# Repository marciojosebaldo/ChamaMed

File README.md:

# ChamaMed
Protótipo de gestão de solicitações de atendimento da enfermagem por parte de pacientes internados em leitos hospitalares.

Recursos:
- Arduino Mega 2560;
- protoboard 830 pontos;
- módulo RFID RC522;
- condutores;
- 3 LEDs 3mm;
- 3 resistores de 680;
- 6 reguladores de 5V (o envio do sinal era de 12V);
- 1 bipe de placa-mãe desktop;
- 1 cabo USB;

Recurso autoral:
- Placa de circuito impresso com relé, transistor 13007 NPN, fotoacoplador, resistor de 220ohm, resistor de 680ohm, conector jack de força PJ-102 horizontal, micro botão de pressão NA, LED 3mm e 3 conectores fêmeas.

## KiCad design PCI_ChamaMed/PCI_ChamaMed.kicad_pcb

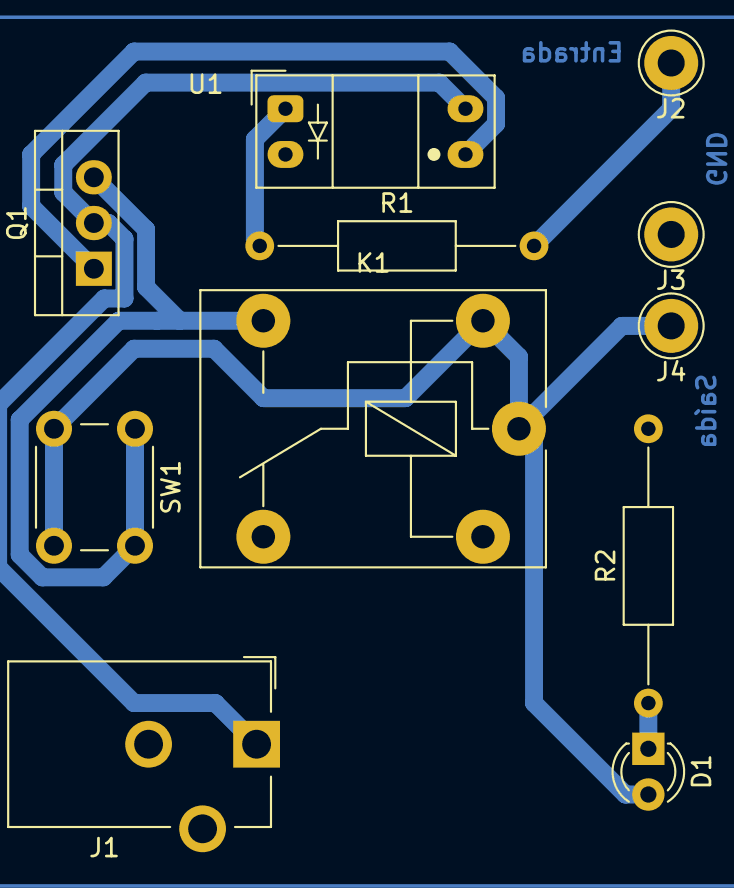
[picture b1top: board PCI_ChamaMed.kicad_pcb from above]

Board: 2 copper layers, 11 parts (0 on the bottom side), 8 nets.

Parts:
D1: LED - 3mm; LED_D3.0mm
J1: Conn_01x02_MountingPin; BarrelJack_CUI_PJ-102AH_Horizontal
J2, J3, J4: Conn_01x01_Pin; Pin_D1.3mm_L11.0mm_LooseFit
K1: RAYEX-L90S; Relay_SPDT_Finder_36.11
Q1: MJE13007G; TO-220-3_Vertical
R1: 220R; R_Axial_DIN0207_L6.3mm_D2.5mm_P15.24mm_Horizontal
R2: 680R; R_Axial_DIN0207_L6.3mm_D2.5mm_P15.24mm_Horizontal
SW1: SW_Push; SW_PUSH_6mm
U1: NSL-32; Everlight_ITR9608-F

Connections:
Earth: J1.2, J3.1, K1.A2, R2.2, U1.2 (K)
unnamed: D1.2 (A), J4.1, K1.11, K1.A1, SW1.2
unnamed: D1.1 (K), R2.1
unnamed: J1.1, Q1.2 (C), U1.4 (R)
unnamed: J2.1, R1.2
unnamed: Q1.1 (B), U1.3 (R)
unnamed: K1.14, Q1.3 (E), SW1.1
unnamed: R1.1, U1.1 (A)

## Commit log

2023-09-19 Add files via upload
    Pseudo hello world
2023-09-20 Delete A_LeitoRapido directory
    Nome incorreto
2023-09-22 Java
